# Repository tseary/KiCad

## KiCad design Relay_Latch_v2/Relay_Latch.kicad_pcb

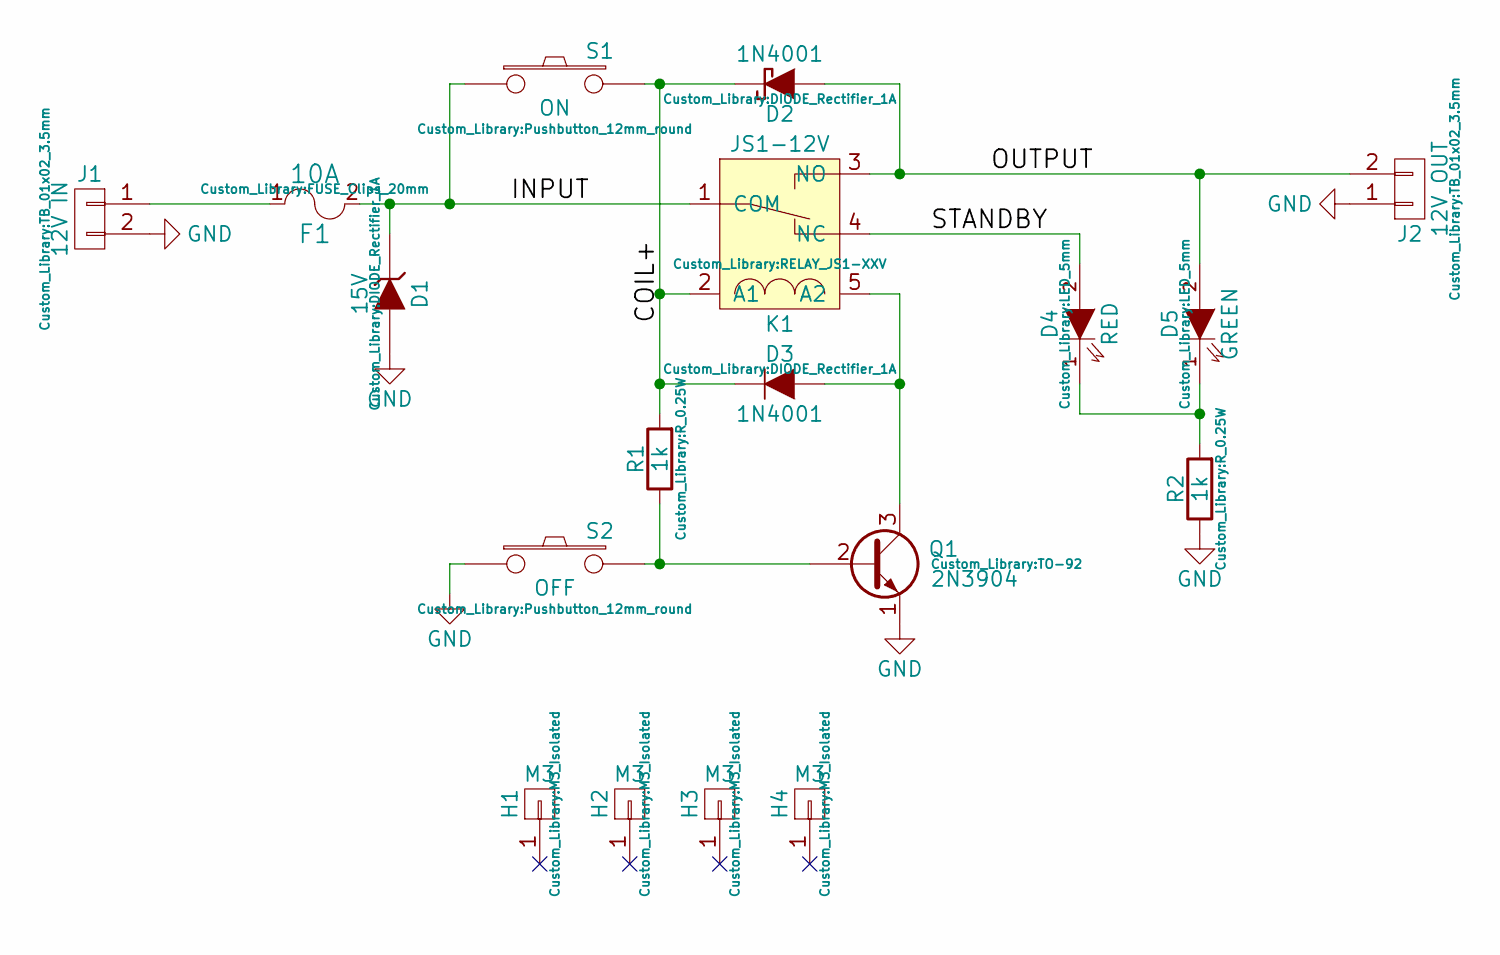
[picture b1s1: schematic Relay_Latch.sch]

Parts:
D1: 15V; DIODE_Rectifier_1A
D2, D3: 1N4001; DIODE_Rectifier_1A
D4: RED; LED_5mm
D5: GREEN; LED_5mm
F1: 10A; FUSE_Clips_20mm
H1, H2, H3, H4: M3; M3_Isolated
J1: 12V IN; TB_01x02_3.5mm
J2: 12V OUT; TB_01x02_3.5mm
K1: JS1-12V; RELAY_JS1-XXV
Q1: 2N3904; TO-92
R1, R2: 1k; R_0.25W
S1: ON; Pushbutton_12mm_round
S2: OFF; Pushbutton_12mm_round

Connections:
/COIL+: D2.1 (K), D3.1 (K), K1.2 (A1), R1.2, S1.2
/INPUT: D1.1 (K), F1.2, K1.1 (COM), S1.1
/OUTPUT: D2.2 (A), D5.2 (A), J2.2, K1.3 (NO)
/STANDBY: D4.2 (A), K1.4 (NC)
GND: D1.2 (A), J1.2, J2.1, Q1.1 (E), R2.1, S2.1
unnamed: D3.2 (A), K1.5 (A2), Q1.3 (C)
unnamed: D4.1 (K), D5.1 (K), R2.2
unnamed: F1.1, J1.1
unnamed: Q1.2 (B), R1.1, S2.2

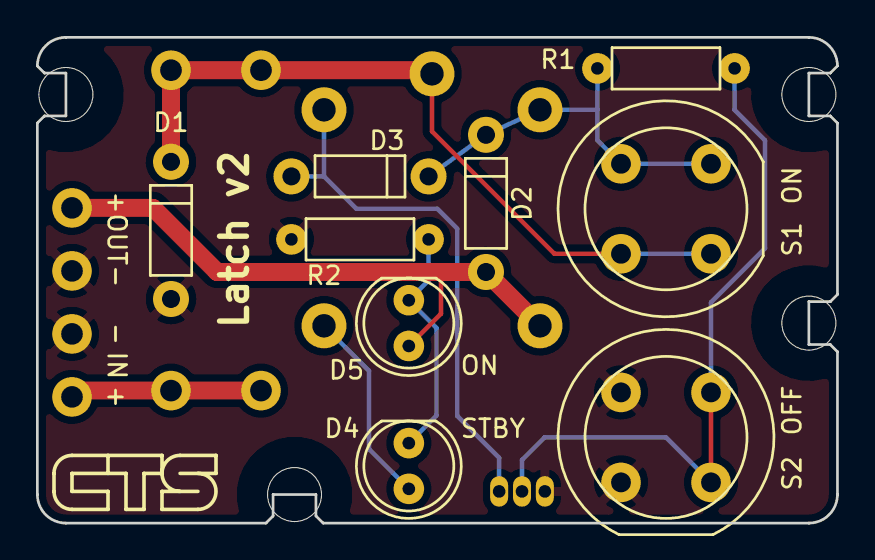
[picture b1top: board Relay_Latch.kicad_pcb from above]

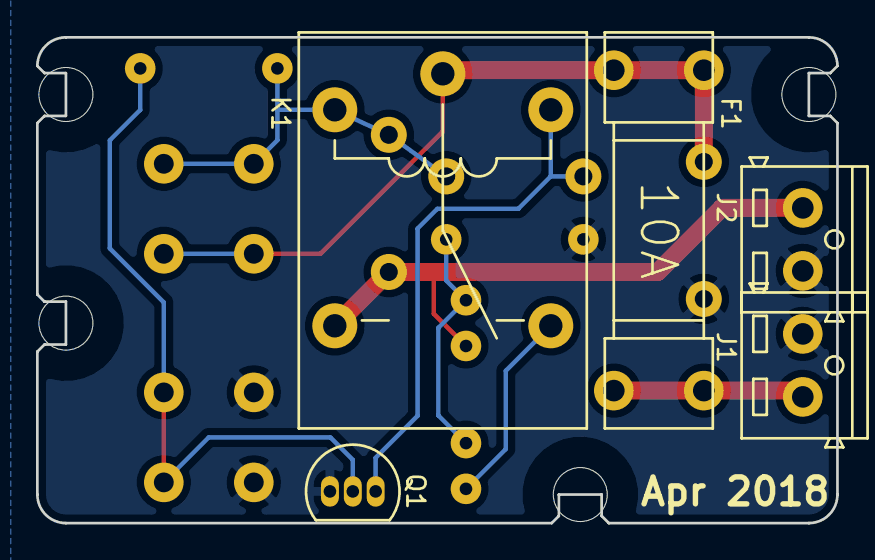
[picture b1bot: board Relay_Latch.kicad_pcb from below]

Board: 2 copper layers, 44.5 x 27.0 mm, 18 parts (5 on the bottom side), 9 nets.

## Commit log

2018-05-30 Relay Latch v2
    Initial commit.
2018-05-30 Added schematic screenshot
